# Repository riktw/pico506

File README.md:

# Pico506 changes

This repo adds a PCB that can be used to replace an existing MFM HDD.
It also adds support for 4 HEAD lines instead of 2 and for drive select support in hardware

This is tested with an MFM emulator, but does not always work in machines, and has not been tested with many computers. Use at your own risk!
If you own a LOT of MFM computers and want to help test it, please make an issue or contact me!

# Pico506

The smallest and cheapest ST-506/RLL/MFM hard drive emulator.

*Read the full story of building this
project: [Emulating a 1987 proprietary RLL hard drive](https://kuba.szczodrzynski.pl/posts/toshiba-t1200/rll-hdd-emulator/)*

## Introduction

Pico506 is a simple, yet universal emulator of old RLL/MFM hard drives using the ST-506 signaling and control interface.

It is based on a Raspberry Pi Pico (RP2040 chip), which makes it extremely cheap to build. Thanks to the PIO
peripheral (Programmable I/O), it also offers pretty good performance and stability.

While it's primarily built to emulate a proprietary RLL(2,7) hard drive made by JVC (JD-3824), which uses a proprietary
26-pin interface, it should also be able to emulate any other drive using ST-506-compatible signaling.

As an added bonus, the Pico506 outputs a signal to drive a small piezo buzzer. This is inspired by
the [HDD Clicker](https://www.vogons.org/viewtopic.php?t=90047) and makes the emulator output "click" sounds whenever
the virtual drive is accessed.

## Prerequisites

While there is no dedicated hardware (PCB) for this project (yet), it is pretty simple to build on a perfboard. The
basic parts required are:

- Raspberry Pi Pico (or similar board with RP2040),
- SD/microSD card and a matching socket (MMC is not supported),
- a connector for the HDD controller of your PC,
- a level shifter/inverter circuit (more on that later),
- a piezo buzzer (without a built-in generator) - optional.

## Interface

The ST-506 interface uses a few control signals - it's probably best to refer to, for example,
Wikipedia ([ST-506/ST-412](https://en.wikipedia.org/wiki/ST-506/ST-412)) to learn more about the control interface.

At this point it's also worth to know the definitions of these common terms:

- **track** - a string of bits (flux transitions) stored on one side of a single HDD platter,
- **head** - a magnetic reading/writing head (like in a cassette player) that accesses one side of a single platter,
- **cylinder** - used to refer to the same track on all sides and all platters; in other words,
  `track length * head count = cylinder length`,
- **sector** - a logical part of one track that holds actual data.

To summarize, here are the most important control signals:

- `DRIVE_SELECT0/1/2/3` - selects one of at most four drives that the PC controller wants to talk to,
- `DRIVE_SELECTED` - indicates that the drive exists and is now selected,
- `HEAD_SELECT0/1/2/3` - up to four lines, which together form a 4-bit number of the currently selected head,
- `READY` - whether the drive has finished the spin-up,
- `TRACK_0` - whether the read/write head is positioned on track/cylinder 0,
- `INDEX` - pulse indicating the beginning of the current track (i.e. next sector will be the first on this track),
- `STEP` - performs a single-track step in the direction indicated by `DIR_IN`,
- `SEEK_COMPLETE` - whether the requested seek has been completed,
- `WRITE_GATE` - makes the head write data to the current track,
- `WRITE_FAULT` - indicates a problem during writing.

You might have noticed that the control signals are usually prefixed by `/` or `~`. This means that they are
active-low - a low voltage (~0V) on the line means "active", and high voltage (~5V) means "inactive". More on that
later.

The data signals are raw bit streams of magnetic flux transitions of the HDD's platters. The bits themselves, however,
depend on the type of encoding used in a particular hard drive -
see [Run-length limited](https://en.wikipedia.org/wiki/Run-length_limited) (RLL), or one of its common
variants, [Modified frequency modulation](https://en.wikipedia.org/wiki/Modified_frequency_modulation) (MFM).

Because the control signals are usually the same (or similar) across different drives (even when using different
encodings), Pico506 doesn't actually care about the data stored on the drive.

Instead, it transparently captures bit streams on the `WRITE` line and outputs them back on the `READ` line. The bit
data of the currently loaded cylinder is kept in RAM. Upon seeking, the modified data (if any) is written to the SD
card, and a new cylinder is loaded.

## Pin mapping

This is the default GPIO mapping used in the published source code. It can be changed freely (in `config.h`), under a
condition that `INDEX` and `SERVO_GATE` are using adjacent GPIOs (if you're using that signal, that is).

| GPIO | Direction | Function            |
|------|-----------|---------------------|
| GP0  | OUT       | UART TX             |
| GP1  | IN        | UART RX             |
| GP2  | IN        | HDD `WRITE_GATE`    |
| GP3  | IN        | HDD `WRITE`         |
| GP4  | IN        | HDD `HEAD_1`        |
| GP5  | OUT       | HDD `READ`          |
| GP6  | OUT       | HDD `INDEX`         |
| GP7  | OUT       | HDD `SERVO_GATE`    |
| GP8  | OUT       | HDD `READY`         |
| GP9  | OUT       | HDD `TRACK_0`       |
| GP10 | OUT       | HDD `SEEK_COMPLETE` |
| GP11 | IN        | HDD `SELECT`        |
| GP12 | IN        | HDD `STEP`          |
| GP13 | IN        | HDD `DIR_IN`        |
| GP15 | OUT       | Buzzer (optional)   |
| GP18 | OUT       | SD `SCK`            |
| GP19 | OUT       | SD `MOSI`           |
| GP20 | IN        | SD `MISO`           |
| GP21 | OUT       | SD `CS`             |

All the signals use **active-high** logic - that is, **opposite** to the normal ST-506 interface. This makes it
necessary to use an inverter, which fortunately also solves the problem of level shifting (3.3V vs 5V).

The inverter chip must be open-drain/open-collector. I personally tested it with 74LS05 and found that it works great.

Here's a simple connection diagram using two 74LS05s:

```
                                    +---------+
                       /WRITE_GATE -| o       |- +5V
 +3V3 ------[/\/\1k/\/\]------ GP2 -|         |- /WRITE
                           /HEAD_1 -|         |- GP3 ------[/\/\1k/\/\]------ +3V3
 +3V3 ------[/\/\1k/\/\]------ GP4 -|         |- GP5
                               GP6 -|         |- /READ ------[/\/\470/\/\]------ +5V
                            /INDEX -|         |- GP7
                               GND -|         |- /SERVO_GATE
                                    +---------+

                                    +---------+
                               GP8 -| o       |- +5V
                            /READY -|         |- GP9
                              GP10 -|         |- /TRACK_0
                    /SEEK_COMPLETE -|         |- /SELECT
                             /STEP -|         |- GP11 ------[/\/\1k/\/\]------ +3V3
+3V3 ------[/\/\1k/\/\]------ GP12 -|         |- /DIR_IN
                               GND -|         |- GP13 ------[/\/\1k/\/\]------ +3V3
                                    +---------+
```

The 1 kOhm pull-up resistors are necessary to make the inverters fast enough when converting 5V to 3.3V.

The 470 Ohm resistor on the `/READ` line is theoretically optional, and you might need to tweak the value a little bit.
A lower value makes the resulting inverted pulses "faster" (i.e. propagation is quicker, so pulses get longer).

As for the `SERVO_GATE` signal (which is not part of the ST-506 specification) - it's a special signal required for the
RLL(2,7) JVC JD-3824 drive. These drivers have 17 "pulses" per track, with 2 sectors between each "pulse". This pulse is
exactly what the `SERVO_GATE` signal means - between every two `INDEX` pulses, there are 17 `SERVO_GATE` pulses. For
emulating an ST-506 drive, this can be left unconnected.

Here's a little visualization of the JVC RLL interface:

```
INDEX         ___/‾‾‾‾‾‾‾‾‾‾‾‾\________________________________________________________
SERVO_GATE    ___/‾‾‾‾‾‾‾‾‾‾‾‾\____________________________________/‾‾‾‾‾‾‾‾‾‾‾‾\_______
READ          .../‾‾‾‾‾‾‾‾‾‾‾‾\....<...data...>....<...data...>..../‾‾‾‾‾‾‾‾‾‾‾‾\....... (repeat 17 times)
```

## Data configuration

Now, this is something that is specific to each hard drive, as it defines the geometry and timing of the signals.

The emulator assumes that each "logical" data bit encodes as 2 bits in MFM and RLL encodings. The entries named `LBYTES`
represent counts of "logical" data bytes (e.g. 512 for sector length).

To convert "logical" bytes into a real duration (in nanoseconds), use the following formula:

```
LENGTH_NS = (1 / (DATA_RATE * 2)) * (LBYTES * 8 * 2) * 1000 * 1000 * 1000
```

(8 - bits per byte, 2 - overhead of RLL/MFM encoding).

Configuration options (`config.h`) that should be adapted to each drive type:

- `DATA_RATE` - data transfer rate, in bits/second. Most MFM drives use 5 Mbps, and RLL(2,7) drives use 7.5 Mbps.
- `MARK_LBYTES` - length of the `INDEX` and `SERVO_GATE` pulses; use the formula above to convert. If in doubt, go for
  around 50 microseconds = 50,000 nanoseconds.
- `HEADER_LBYTES` - length of the sector header; using around 100 should be good.
- `DATA_LBYTES` - length of the sector data; should be 512 for most drives.
- `SECTORS_PER_PULSE` - see: `SERVO_GATE` description above. Use `1` unless emulating a JD-3824 drive, then use `2`.
- `PULSES_PER_TRACK` - in other words: `sectors per track = sectors per pulse * pulses per track`.
- `HEADS` - self-explanatory.
- `CYLINDERS` - self-explanatory.

## Limitations

1. Since the emulator doesn't decode RLL/MFM data (it uses raw bit streams), the total sector count in a single cylinder
   cannot exceed the available RAM space. To calculate total RAM usage for one cylinder (in bytes), use:
   `(MARK_LBYTES + (HEADER_LBYTES + SECTOR_LBYTES) * SECTORS_PER_PULSE) * PULSES_PER_TRACK * 8 * 2 * HEADS / 8`.
2. Because of above, the RAM usage for a single cylinder is about 2.5x bigger than the actual data stored in these bits.
   This also makes seek times longer, because more data has to be read from the SD card.
3. Only two heads are supported so far (the head switching code for more than 1 bit is not implemented). This is,
   however, pretty easy to fix - just add more GPIOs and supporting code in `st506_head_irq()`.
4. Drive Select is not supported, i.e. the drive acts as if it was selected all the time. It shouldn't be a problem
   when
   using a single drive with an RLL/MFM controller card, but multiple drives will conflict with each other. A proper
   solution would be to use NAND gates to offload the drive selection from software.
5. `WRITE_FAULT` is not implemented.
6. There is currently no way to change the HDD image on-the-fly; the image filename is hardcoded in `pico506.c`.

## Screenshots

Here are some screenshots of the RLL(2,7) emulator in action, in a Toshiba T1200:

## License

This project is licensed under the [General Public License](LICENSE).

Copyright © 2025 Kuba Szczodrzyński

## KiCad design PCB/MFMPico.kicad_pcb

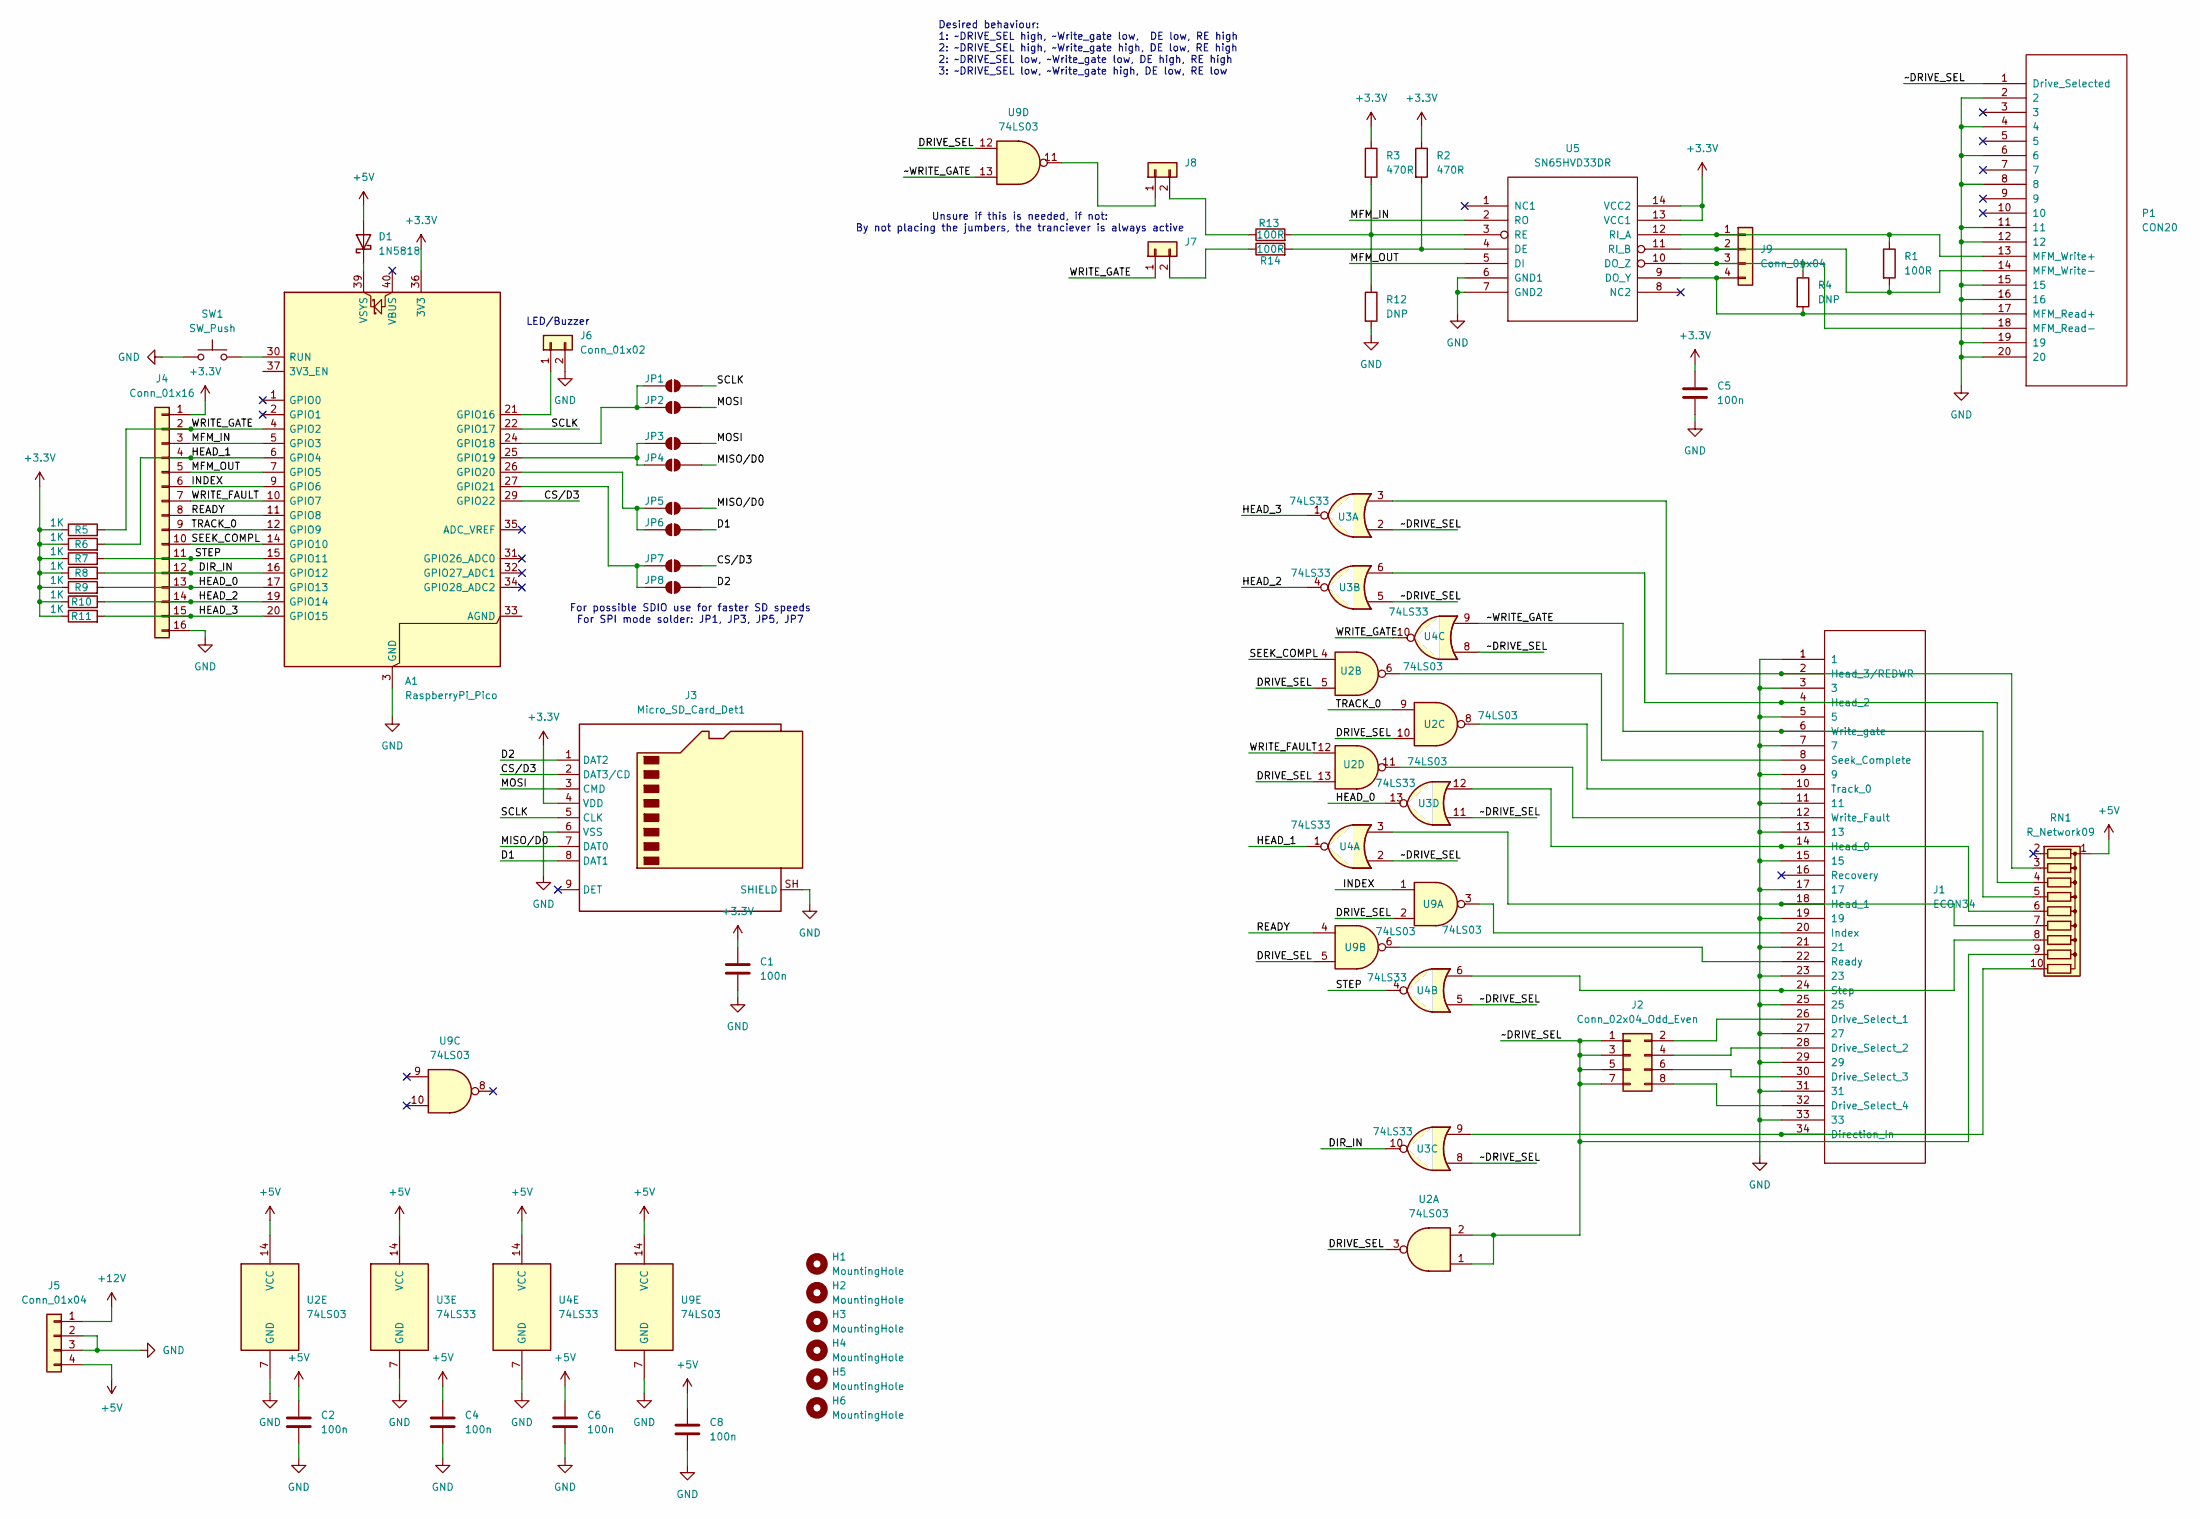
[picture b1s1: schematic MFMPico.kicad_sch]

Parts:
A1: RaspberryPi_Pico; RaspberryPi_Pico_Common_Unspecified
C1, C2, C4, C5, C6, C8: 100n; C_0603_1608Metric_Pad1.08x0.95mm_HandSolder
D1: 1N5818; D_DO-41_SOD81_P10.16mm_Horizontal
H1, H2, H3, H4, H5, H6: MountingHole; MountingHole_3.2mm_M3
J1: ECON34
J2: Conn_02x04_Odd_Even; PinHeader_2x04_P2.54mm_Vertical
J3: Micro_SD_Card_Det1; microSD Hanbo Electronic TF-018
J4: Conn_01x16; PinHeader_1x16_P2.54mm_Vertical
J5: Conn_01x04; DRVPWR
J6: Conn_01x02; PinHeader_1x02_P2.54mm_Vertical
J7: DNP; PinHeader_1x02_P2.54mm_Vertical
J8: PLACE; PinHeader_1x02_P2.54mm_Vertical
J9: Conn_01x04; PinHeader_1x04_P2.54mm_Vertical
JP1, JP2, JP3, JP4, JP5, JP6, JP7, JP8: SolderJumper_2_Open; SolderJumper-2_P1.3mm_Open_Pad1.0x1.5mm
P1: CON20; econ20
R1, R13, R14: 100R; R_0603_1608Metric
R2, R3: 470R; R_0603_1608Metric
R4, R12: DNP; R_0603_1608Metric
R5, R6, R7, R8, R9, R10, R11: 1K; R_0603_1608Metric
RN1: R_Network09; R_Array_SIP10
SW1: SW_Push; SW_PUSH_6mm
U2, U9: 74LS03; DIP-14_W7.62mm
U3, U4: 74LS33; DIP-14_W7.62mm
U5: SN65HVD33DR; SOIC-14_3.9x8.7mm_P1.27mm

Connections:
+3.3V: A1.36 (3V3), C1.1, C5.1, J3.4 (VDD), J4.1, R2.1, R3.1, R5.1, R6.1, R7.1, R8.1, R9.1, R10.1, R11.1, U5.13 (VCC1), U5.14 (VCC2)
+5V: C2.1, C4.1, C6.1, C8.1, D1.2 (A), J5.4, RN1.1 (common), U2.14 (VCC), U3.14 (VCC), U4.14 (VCC), U9.14 (VCC)
+12V: J5.1
/CS/D3: A1.29 (GPIO22), J3.2 (DAT3/CD), JP7.2 (B)
/D1: J3.8 (DAT1), JP6.2 (B)
/D2: J3.1 (DAT2), JP8.2 (B)
/DIR_IN: A1.16 (GPIO12), J4.12, R8.2, U3.10
/DRIVE_SEL: U2.3, U2.5, U2.10, U2.13, U9.2, U9.5, U9.12
/HEAD_0: A1.17 (GPIO13), J4.13, R9.2, U3.13
/HEAD_1: A1.6 (GPIO4), J4.4, R6.2, U4.1
/HEAD_2: A1.19 (GPIO14), J4.14, R10.2, U3.4
/HEAD_3: A1.20 (GPIO15), J4.15, R11.2, U3.1
/INDEX: A1.9 (GPIO6), J4.6, U9.1
/MFM_IN: A1.5 (GPIO3), J4.3, U5.2 (RO)
/MFM_OUT: A1.7 (GPIO5), J4.5, U5.5 (DI)
/MISO/D0: J3.7 (DAT0), JP4.2 (B), JP5.2 (B)
/MOSI: J3.3 (CMD), JP2.2 (B), JP3.2 (B)
/READY: A1.11 (GPIO8), J4.8, U9.4
/SCLK: A1.22 (GPIO17), J3.5 (CLK), JP1.2 (B)
/SEEK_COMPL: A1.14 (GPIO10), J4.10, U2.4
/STEP: A1.15 (GPIO11), J4.11, R7.2, U4.4
/TRACK_0: A1.12 (GPIO9), J4.9, U2.9
/WRITE_FAULT: A1.10 (GPIO7), J4.7, U2.12
/WRITE_GATE: A1.4 (GPIO2), J4.2, J7.1, R5.2, U4.10
/~DRIVE_SEL: J2.1, J2.3, J2.5, J2.7, P1.1 (Drive_Selected), RN1.9 (R8), U2.1, U2.2, U3.2, U3.5, U3.8, U3.11, U4.2, U4.5, U4.8
/~WRITE_GATE: J1.6 (Write_gate), RN1.5 (R4), U4.9, U9.13
GND: A1.3 (GND), A1.8 (GND), A1.13 (GND), A1.18 (GND), A1.23 (GND), A1.28 (GND), A1.38 (GND), C1.2, C2.2, C4.2, C5.2, C6.2, C8.2, J1.1, J1.3, J1.5, J1.7, J1.9, J1.11, J1.13, J1.15, J1.17, J1.19, J1.21, J1.23, J1.25, J1.27, J1.29, J1.31, J1.33, J3.6 (VSS), J3.SH (SHIELD), J4.16, J5.2, J5.3, J6.2, P1.2, P1.4, P1.6, P1.8, P1.11, P1.12, P1.15, P1.16, P1.19, P1.20, R12.2, SW1.1, U2.7 (GND), U3.7 (GND), U4.7 (GND), U5.6 (GND1), U5.7 (GND2), U9.7 (GND)
unnamed: A1.21 (GPIO16), J6.1
unnamed: A1.24 (GPIO18), JP1.1 (A), JP2.1 (A)
unnamed: A1.25 (GPIO19), JP3.1 (A), JP4.1 (A)
unnamed: A1.26 (GPIO20), JP5.1 (A), JP6.1 (A)
unnamed: A1.27 (GPIO21), JP7.1 (A), JP8.1 (A)
unnamed: A1.30 (RUN), SW1.2
unnamed: A1.39 (VSYS), D1.1 (K)
unnamed: J1.34 (Direction_In), RN1.10 (R9), U3.9
unnamed: J1.26 (Drive_Select_1), J2.2
unnamed: J1.28 (Drive_Select_2), J2.4
unnamed: J1.30 (Drive_Select_3), J2.6
unnamed: J1.32 (Drive_Select_4), J2.8
unnamed: J1.14 (Head_0), RN1.6 (R5), U3.12
unnamed: J1.18 (Head_1), RN1.7 (R6), U4.3
unnamed: J1.4 (Head_2), RN1.4 (R3), U3.6
unnamed: J1.2 (Head_3/REDWR), RN1.3 (R2), U3.3
unnamed: J1.20 (Index), U9.3
unnamed: J1.22 (Ready), U9.6
unnamed: J1.8 (Seek_Complete), U2.6
unnamed: J1.24 (Step), RN1.8 (R7), U4.6
unnamed: J1.10 (Track_0), U2.8
unnamed: J1.12 (Write_Fault), U2.11
unnamed: J7.2, R14.1
unnamed: J8.1, U9.11
unnamed: J8.2, R13.1
unnamed: J9.1, P1.13 (MFM_Write+), R1.1, U5.12 (RI_A)
unnamed: J9.2, P1.14 (MFM_Write-), R1.2, U5.11 (RI_B)
unnamed: J9.3, P1.18 (MFM_Read-), R4.1, U5.10 (DO_Z)
unnamed: J9.4, P1.17 (MFM_Read+), R4.2, U5.9 (DO_Y)
unnamed: R2.2, R14.2, U5.4 (DE)
unnamed: R3.2, R12.1, R13.2, U5.3 (RE)

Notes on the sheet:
Desired behaviour: 1: ~DRIVE_SEL high, ~Write_gate low, DE low, RE high 2: ~DRIVE_SEL high, ~Write_gate high, DE low, RE high 2: ~DRIVE_SEL low, ~Write_gate low, DE high, RE high 3: ~DRIVE_SEL low, ~Write_gate high, DE low, RE low
For possible SDIO use for faster SD speeds For SPI mode solder: JP1, JP3, JP5, JP7
LED/Buzzer
Unsure if this is needed, if not: By not placing the jumbers, the tranciever is always active

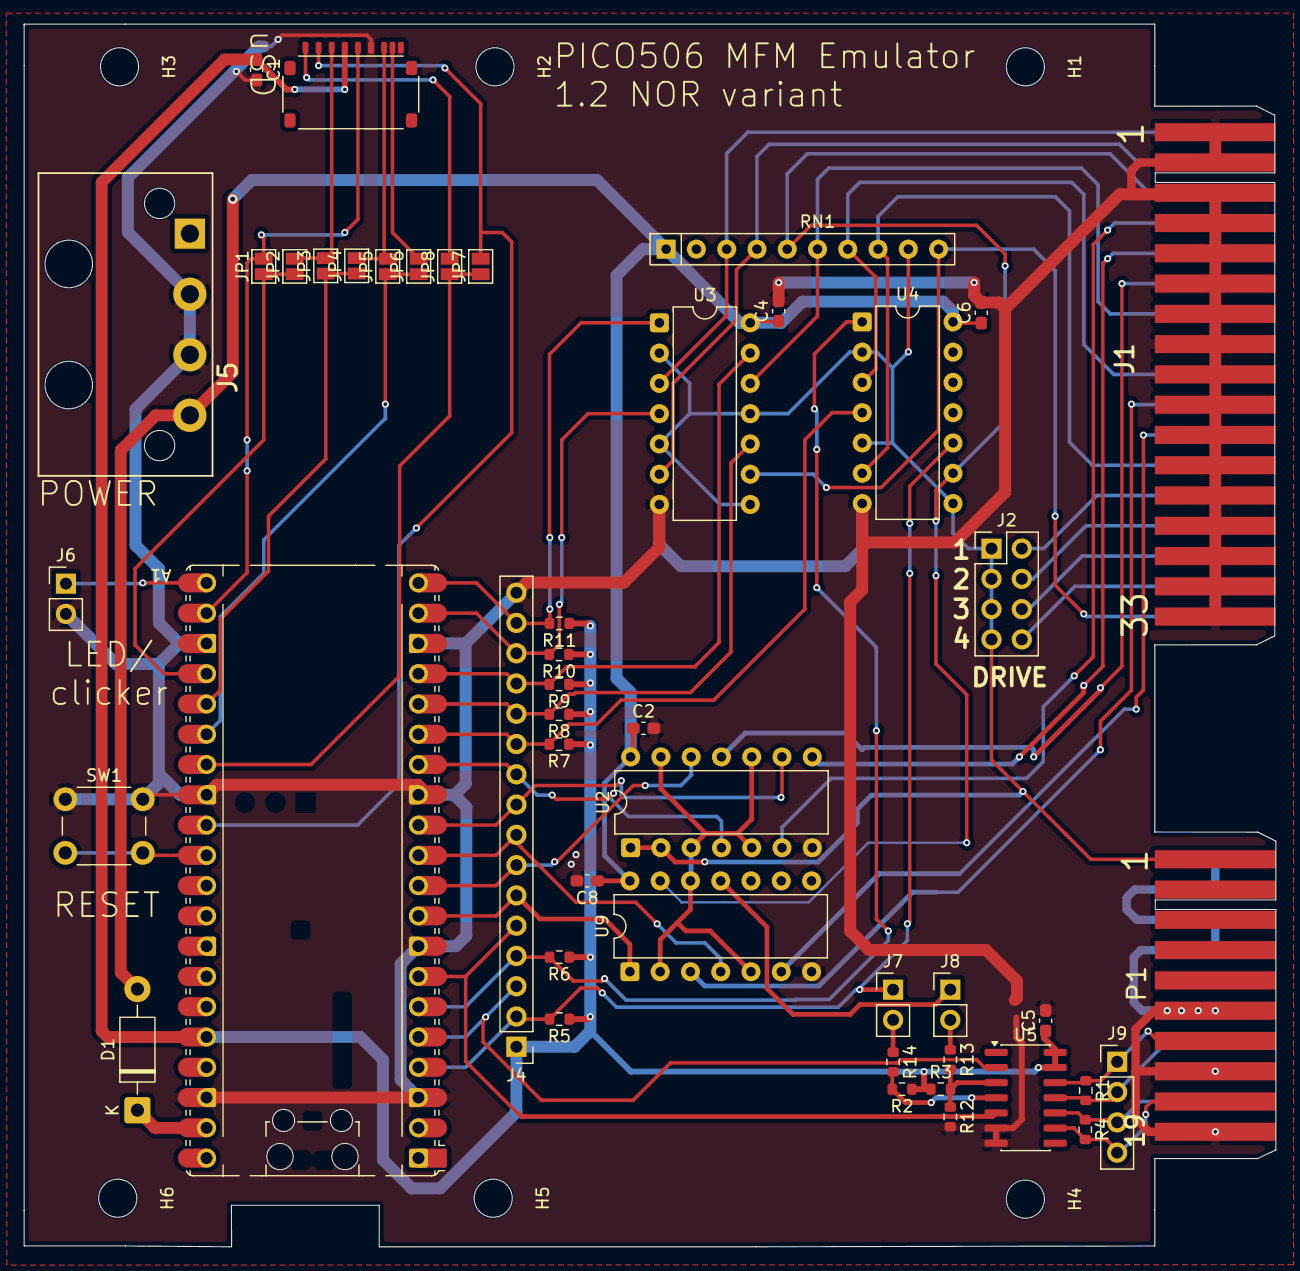
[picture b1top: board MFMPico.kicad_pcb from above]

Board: 2 copper layers, 105.0 x 102.6 mm, 53 parts (0 on the bottom side), 57 nets.

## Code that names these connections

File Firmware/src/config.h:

// Copyright (c) Kuba Szczodrzyński 2025-8-4.

#pragma once

// MFM data
#define PIN_READ		  5
#define PIN_WRITE		  3
// Control Input
#define PIN_WRITE_GATE	  2
#define PIN_HEAD_0		  13
#define PIN_HEAD_1		  4
#define PIN_HEAD_2		  14
#define PIN_HEAD_3		  15
#define PIN_DIR_IN		  12
#define PIN_STEP		  11
// #define DEVICE_SELECT	  17
//  Control Output
#define PIN_SEEK_COMPLETE 10
#define PIN_SERVO_GATE	  7 // unused on MFM
#define PIN_INDEX		  6
#define PIN_WRITEFAULT	  7
#define PIN_TRACK_0		  9
#define PIN_READY		  8
// Buzzer
#define PIN_BUZZER		  16 // moved to 16 from 15
// SD Card
#define PIN_SD_SCK		  18
#define PIN_SD_MOSI		  19
#define PIN_SD_MISO		  20
#define PIN_SD_CS		  21

#define DATA_RATE		  5000000
#define MARK_LBYTES		  42
#define HEADER_LBYTES	  58
#define DATA_LBYTES		  512
#define SECTORS_PER_PULSE 1
#define PULSES_PER_TRACK  17
#define HEADS			  2 // Up to 8 supported
#define CYLINDERS		  322

#define STEP_SETTLE_US 10000

#define MARK_BITS	(MARK_LBYTES * 8 * 2)
#define SECTOR_BITS ((HEADER_LBYTES + DATA_LBYTES) * 8 * 2)
#define PULSE_BITS	(MARK_BITS + SECTOR_BITS * SECTORS_PER_PULSE)
#define TRACK_BITS	(PULSE_BITS * PULSES_PER_TRACK)

#define MARK_WORDS		(MARK_BITS / 32)
#define SECTOR_WORDS	(SECTOR_BITS / 32)
#define PULSE_WORDS		(PULSE_BITS / 32)
#define TRACK_BYTES		(TRACK_BITS / 8)
#define TRACK_WORDS		(TRACK_BYTES / 4)
#define CYLINDER_BYTES	(TRACK_BYTES * HEADS)
#define CYLINDER_BLOCKS (((CYLINDER_BYTES - 1) / 512) + 1)
#define TRACK_BLOCKS	(CYLINDER_BLOCKS / HEADS)
#define DRIVE_BYTES		(CYLINDER_BYTES * CYLINDERS)

#define IDLE_TIMEOUT 5000

#define CYL_INVALID 2048

#define PIO_RDDT pio0
#define PIO_RDGT pio0
#define PIO_STEP pio0
#define PIO_WRDT pio1
#define PIO_WRGT pio1
#define PIO_WRRM pio1

#define SM_RDDT	 0
#define SM_RDGT	 1
#define SM_STEP	 2
#define SM_WRDT	 0
#define SM_WRGT	 1
#define SM_WRRMC 2
#define SM_WRRMA 3

#define PIO_SM_RDDT	 PIO_RDDT, SM_RDDT
#define PIO_SM_RDGT	 PIO_RDGT, SM_RDGT
#define PIO_SM_STEP	 PIO_STEP, SM_STEP
#define PIO_SM_WRDT	 PIO_WRDT, SM_WRDT
#define PIO_SM_WRGT	 PIO_WRGT, SM_WRGT
#define PIO_SM_WRRMC PIO_WRRM, SM_WRRMC
#define PIO_SM_WRRMA PIO_WRRM, SM_WRRMA

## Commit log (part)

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2026-05-24 Moving code to separate folder
2026-05-24 Added initial pcb, finished the code move
2026-05-25 Mostly up to date PCB
2026-05-27 last changes before ordering
2026-05-27 4 heads is always better
